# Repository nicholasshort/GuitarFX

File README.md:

# GuitarFX

This is a digital guitar effects pedal designed as a generic DSP platform. I've written simple algorithms such as volume and tone control, however plans are in the works for others: namely hard and soft clipping, digital delay, and much more. The two knobs control various parameters within the current algorithm, including volume or cutoff frequency.

## Hardware

- **MCU**: STM32H723VGT6 (Cortex-M7 @ 550 MHz)
- **Codec**: TI PCM3060 — 24-bit stereo ADC/DAC
- **Analog I/O**: TLV9161 op-amp buffers with 25 kHz Butterworth anti-aliasing and reconstruction filters
- **Audio**: Standard 1/4" guitar input and output, true-bypass footswitch
- **Controls**: 2 × potentiometers, RGB status LED
- **Power**: 9 V DC barrel jack (USB-C can also power the board for bench work)
- **PCB**: 4-layer, KiCad

## Repository layout

- `GuitarFX-PCB/` — KiCad project (schematics, board, libraries)
- `GuitarFX-PCB/Manufacturing/` — Gerbers, BOM, and pick-and-place files for JLCPCB
- `images/` — Photos of the board and enclosure

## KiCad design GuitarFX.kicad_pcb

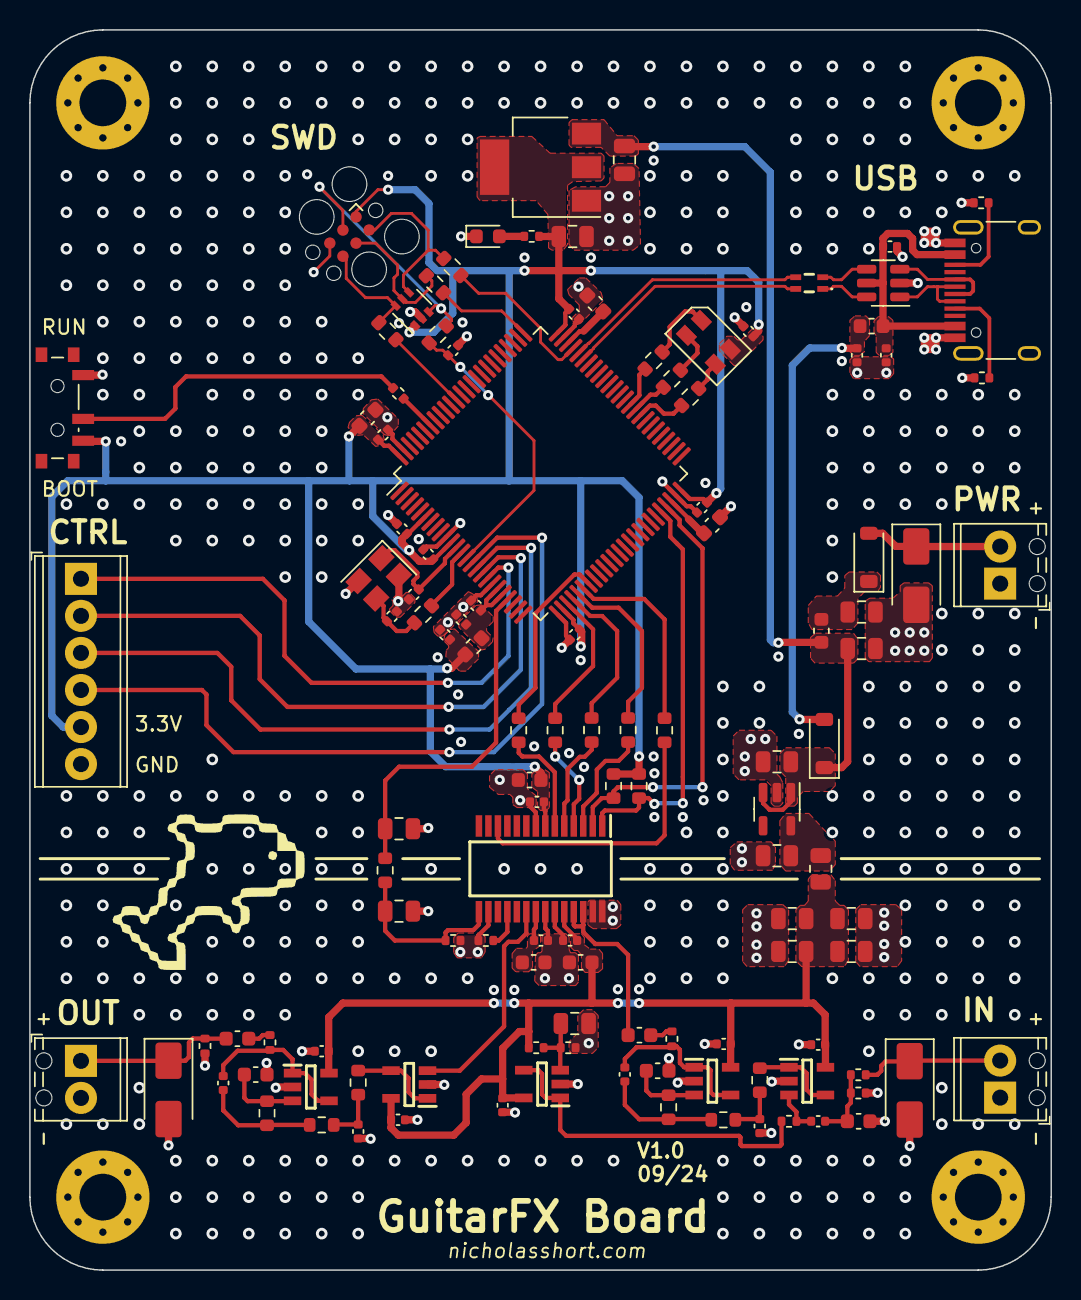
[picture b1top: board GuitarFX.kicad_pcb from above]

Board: 4 copper layers, 70.0 x 85.0 mm, 124 parts (0 on the bottom side), 80 nets.

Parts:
C201, C202, C203, C204: 47uF; C_0805_2012Metric
C205, C206, C207, C208, C411, C412: 2.2uF; C_0805_2012Metric
C209, C210: 10uF; C_0805_2012Metric
C301, C318, C319: 2.2u; C_0603_1608Metric
C302, C303, C304, C305, C306, C307, C308, C309, C310, C311, C312, C313, C316, C317, C402, C403, C404, C420, C421, C429, C431, C433: 100n; C_0402_1005Metric
C314, C315: 10p; C_0402_1005Metric
C401, C409, C419, C423: 1n; C_0402_1005Metric
C405: 22u; C_0805_2012Metric
C406: 10n; C_0402_1005Metric
C407, C422: 4.7u; C_0603_1608Metric
C408, C410, C424: 150p; C_0603_1608Metric
C428, C430, C432: 10u; C_0603_1608Metric
D201, D202: MBR0530; D_SOD-123
D203, D401, D403: SMAJ15A; D_SMA
D204: LED; LED_0603_1608Metric
D302: PESD3V3L5UY; SOT-363_SC-70-6
D303: LED_RGBA; LED_SMD_RGB_AAA3528LSEEZGKQBKS
FB201, FB301, FB302: 120R; L_0603_1608Metric
FL301: ACM2012-900-2P-TL002; ACM20129002PTL002
H101, H102, H103, H104: MountingHole_Pad; MountingHole_3.2mm_M3_Pad_Via
IC401: PCM3060PWR; SOP65P640X120-28N
J202, J401, J402: Screw_Terminal_01x02; TerminalBlock_Phoenix_MPT-0,5-2-2.54_1x02_P2.54mm_Horizontal
J301: USB_C_Receptacle_USB2.0; USB_C_Receptacle_HRO_TYPE-C-31-M-12
J302: Conn_ARM_SWD_TagConnect_TC2030; Tag-Connect_TC2030-IDC-FP_2x03_P1.27mm_Vertical
J303: Screw_Terminal_01x06; TerminalBlock_Phoenix_MPT-0,5-6-2.54_1x06_P2.54mm_Horizontal
R201: 10R; R_0805_2012Metric
R202, R401, R403, R404: 1k; R_0402_1005Metric
R301, R427, R429: 10k; R_0402_1005Metric
R302, R305, R306, R307, R308, R419, R420, R424, R426, R428: 0R; R_0603_1608Metric
R303, R304: 5.1k; R_0402_1005Metric
R309, R310: 325R (300R); R_0603_1608Metric
R311: 750R; R_0603_1608Metric
R402, R409: 1M; R_0402_1005Metric
R405, R421: 8.2k; R_0603_1608Metric
R406, R422: 27k; R_0603_1608Metric
R407, R423: 15k; R_0603_1608Metric
R408, R425: 100R; R_0402_1005Metric
R410: 100k; R_0402_1005Metric
R411: 5.1k; R_0603_1608Metric
R417, R418: 10k; R_0603_1608Metric
SW301: SW_SPDT; SW_SPDT_PCM12
U201: NCP718xSN500; SOT-23-5
U202: NCP1117-3.3_SOT223; SOT-223-3_TabPin2
U301: USBLC6-2SC6; SOT-23-6
U303: STM32H723VGTx; LQFP-100_14x14mm_P0.5mm
U401, U402, U403, U406, U407: TLV9161IDBVR; SOT95P280X145-5N
Y301: 24MHz; Crystal_SMD_3225-4Pin_3.2x2.5mm

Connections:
+3.3V: C209.1, C301.1, C302.1, C303.1, C304.1, C305.1, C306.1, C307.1, C310.1, C317.1, C428.1, C429.1, D302.1 (K1), D303.4 (A), FB301.2, IC401.7 (VDD), J302.1 (VCC), J303.5, R202.1, R417.1, R418.1, SW301.3 (C), U202.2 (VO), U303.6 (VBAT), U303.11 (VDD), U303.27 (VDD), U303.50 (VDD), U303.75 (VDD), U303.100 (VDD)
+5V: C208.1, R201.1, U201.5 (OUT)
+5VA: C201.1, C202.1, C203.1, C204.1, C402.1, C403.1, C404.1, C420.1, C421.1, C430.1, C431.1, IC401.24 (VCC), R201.2, R401.1, U401.5 (V+), U402.5 (V+), U403.5 (V+), U406.5 (V+), U407.5 (V+)
/Codec/AUDIO_VIN: D401.1 (A1), J401.2, R404.1
/Codec/AUDIO_VOUT: C422.1, D403.1 (A1), J402.1, R427.2
/Codec/CODEC_BCK1: IC401.5 (BCK1), R424.2
/Codec/CODEC_DIN: IC401.12 (DIN), R428.2
/Codec/CODEC_DOUT: IC401.3 (DOUT), R419.2
/Codec/CODEC_LRCK1: IC401.4 (LRCK1), R420.2
/Codec/CODEC_SCK1: IC401.6 (SCKI1), R426.2
/Codec/CODEC_VCOM: C432.1, C433.1, IC401.21 (VCOM)
/Codec/CODEC_VIN: C407.1, IC401.25 (VINL), IC401.26 (VINR)
/Codec/CODEC_VOUT: IC401.20 (VOUTL+), U406.3 (+)
/Codec/IN_AA_BUFF_IN: C410.1, R407.2, U403.3 (+)
/Codec/IN_AA_BUFF_OUT: C401.1, R408.1, U403.1, U403.4 (-)
/Codec/IN_BUF_IN: C406.2, R402.1, U402.3 (+)
/Codec/IN_BUF_OUT: R405.1, U402.1, U402.4 (-)
/Codec/IN_RF: C406.1, C408.1, R404.2, R409.2
/Codec/NRST_FILT: C412.1, IC401.15 (~RST), R411.2, R429.1
/Codec/OUT_AA_BUFF_IN: C424.1, R423.2, U407.3 (+)
/Codec/OUT_AA_BUFF_OUT: C419.1, R425.1, U407.1, U407.4 (-)
/Codec/OUT_BUF_OUT: R421.1, U406.1, U406.4 (-)
/Codec/VREF: C405.1, R401.2, R403.1, U401.3 (+)
/MCU/ADC3_INP0: J303.2, U303.17 (PC2_C)
/MCU/ADC3_INP1: J303.1, U303.18 (PC3_C)
/MCU/ADC3_INP10: J303.4, U303.15 (PC0)
/MCU/ADC3_INP11: J303.3, U303.16 (PC1)
/MCU/BOOT0: R301.2, U303.94 (BOOT0)
/MCU/HSE_IN: C314.1, U303.12 (PH0), Y301.1
/MCU/HSE_OUT: R302.2, U303.13 (PH1)
/MCU/LED_B: D303.3 (BK), R309.2
/MCU/LED_G: D303.2 (GK), R310.2
/MCU/LED_R: D303.1 (RK), R311.2
/MCU/MCU_NRST: C316.1, R308.1, U303.14 (NRST)
/MCU/MCU_SWCLK: R306.1, U303.76 (PA14(JTCK)
/MCU/MCU_SWDIO: R305.1, U303.72 (PA13(JTMS)
/MCU/MCU_SWO: R307.1, U303.89 (PB3(JTDO)
/MCU/MCU_VCAP1: C318.1, U303.48 (VCAP)
/MCU/MCU_VCAP2: C319.1, U303.73 (VCAP)
/MCU/NRST: D302.3 (K2), J302.3 (~RESET), R308.2
/MCU/SWCLK: D302.5 (K4), J302.4 (SWCLK), R306.2
/MCU/SWDIO: D302.4 (K3), J302.2 (SWDIO), R305.2
/MCU/SWO: D302.6 (K5), J302.6 (SWO), R307.2
/MCU/TIM4_CH1: R309.1, U303.59 (PD12)
/MCU/TIM4_CH2: R310.1, U303.60 (PD13)
/MCU/TIM4_CH3: R311.1, U303.61 (PD14)
/MCU/USB_CMC_D+: FL301.2, U301.4 (I/O2)
/MCU/USB_CMC_D-: FL301.1, U301.6 (I/O1)
/MCU/USB_CON_CC1: J301.A5 (CC1), R303.1
/MCU/USB_CON_CC2: J301.B5 (CC2), R304.1
/MCU/USB_CON_D+: J301.A6 (D+), J301.B6 (D+), U301.3 (I/O2)
/MCU/USB_CON_D-: J301.A7 (D-), J301.B7 (D-), U301.1 (I/O1)
/MCU/USB_FS_D+: FL301.3, U303.71 (PA12)
/MCU/USB_FS_D-: FL301.4, U303.70 (PA11)
/Power/R_LED: D204.2 (A), R202.2
/Power/VCC_FILT: C206.1, C207.1, C210.1, D201.1 (K), FB201.2, U201.1 (IN), U201.3 (EN), U202.3 (VI)
/Power/VCC_RP: C205.1, D202.1 (K), FB201.1
CODEC_NRST: C411.1, R411.1, U303.22 (PA0)
GND: C201.2, C202.2, C203.2, C204.2, C205.2, C206.2, C207.2, C208.2, C209.2, C210.2, C301.2, C302.2, C303.2, C304.2, C305.2, C306.2, C307.2, C308.2, C309.2, C310.2, C311.2, C312.2, C313.2, C314.2, C315.2, C316.2, C317.2, C318.2, C319.2, C402.2, C403.2, C404.2, C405.2, C408.2, C409.2, C410.2, C411.2, C412.2, C420.2, C421.2, C423.2, C424.2, C428.2, C429.2, C430.2, C431.2, C432.2, C433.2, D203.2 (A2), D204.1 (K), D302.2 (A), D401.2 (A2), D403.2 (A2), H101.1, H102.1, H103.1, H104.1, IC401.8 (DGND), IC401.16 (SGND), IC401.22 (AGND2), IC401.23 (AGND1), IC401.27 (~MS/ADR/IFMD), IC401.28 (MODE), J202.1, J301.A1 (GND), J301.A12 (GND), J301.B1 (GND), J301.B12 (GND), J302.5 (GND), J303.6, J401.1, J402.2, R303.2, R304.2, R403.2, R409.1, R410.2, R427.1, R429.2, SW301.1 (A), U201.2 (GND), U202.1 (GND), U301.2 (GND), U303.10 (VSS), U303.19 (VSSA), U303.26 (VSS), U303.49 (VSS), U303.74 (VSS), U303.99 (VSS), U401.2 (V-), U402.2 (V-), U403.2 (V-), U406.2 (V-), U407.2 (V-), Y301.2, Y301.4
I2C1_SCL: IC401.1 (MC/SCL/FMT), R417.2, U303.46 (PB10)
I2C1_SDA: IC401.2 (MD/SDA/DEMP), R418.2, U303.47 (PB11)
I2S1_CK: R424.1, U303.29 (PA5)
I2S1_MCK: R426.1, U303.32 (PC4)
I2S1_SDI: R419.1, U303.30 (PA6)
I2S1_SDO: R428.1, U303.31 (PA7)
I2S1_WS: R420.1, U303.28 (PA4)
unnamed: C315.1, R302.1, Y301.3
unnamed: C401.2, R406.2, R407.1
unnamed: C407.2, R408.2
unnamed: C409.1, R405.2, R406.1
unnamed: C419.2, R422.2, R423.1
unnamed: C422.2, R425.2
unnamed: C423.1, R421.2, R422.1
unnamed: IC401.18 (VOUTR+), R410.1
unnamed: R301.1, SW301.2 (B)
VBUS: C311.1, C313.1, FB302.1, J301.A4 (VBUS), J301.A9 (VBUS), J301.B4 (VBUS), J301.B9 (VBUS), U301.5 (VBUS)
VCC: D202.2 (A), D203.1 (A1), J202.2
VCOM: R402.2, U401.1, U401.4 (-)
VDDA: C308.1, C309.1, FB301.1, U303.20 (VREF+), U303.21 (VDDA)
VUSB_FILT: C312.1, D201.2 (A), FB302.2

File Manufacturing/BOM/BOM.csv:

Comment,Designator,Footprint,JLCPCB Part #
47uF Unpolarized capacitor,"C201,C202,C203,C204",C_0805_2012Metric,C108659
2.2uF Unpolarized capacitor,"C205,C206,C207,C208,C411,C412",C_0805_2012Metric,C77081
10uF Unpolarized capacitor,"C209,C210",C_0805_2012Metric,C90543
2.2u Unpolarized capacitor,"C301,C318,C319",C_0603_1608Metric,C71001
100n Unpolarized capacitor,"C302,C303,C304,C305,C306,C307,C308,C309,C310,C311,C312,C313,C316,C317,C402,C403,C404,C420,C421,C429,C431,C433",C_0402_1005Metric,C432917
10p Unpolarized capacitor,"C314,C315",C_0402_1005Metric,C258501
1n Unpolarized capacitor,"C401,C409,C419,C423",C_0402_1005Metric,C106205
22u Unpolarized capacitor,C405,C_0805_2012Metric,C129303
10n Unpolarized capacitor,C406,C_0402_1005Metric,C386111
4.7u Unpolarized capacitor,"C407,C422",C_0603_1608Metric,C77045
150p Unpolarized capacitor,"C408,C410,C424",C_0603_1608Metric,C126577
10u Unpolarized capacitor,"C428,C430,C432",C_0603_1608Metric,C380314
"MBR0530 30V 0.5A Schottky Power Rectifier Diode, SOD-123","D201,D202",D_SOD-123,C77336
"SMAJ15A 400W unidirectional Transient Voltage Suppressor, 15.0Vr, SMA(DO-214AC)","D203,D401,D403",D_SMA,C908769
LED Light emitting diode,D204,LED_0603_1608Metric,C5123548
"PESD3V3L5UY Low capacitance unidirectional fivefold ESD protection diode array, 3.3V, Common Anode, SOT-363",D302,SOT-363_SC-70-6,C3021133
"LED_RGBA RGB LED, red/green/blue/anode",D303,LED_SMD_RGB_AAA3528LSEEZGKQBKS,C5547384
120R Ferrite bead,"FB201,FB301,FB302",L_0603_1608Metric,C12391
ACM2012-900-2P-TL002 Common Mode Chokes / Filters -,FL301,ACM20129002PTL002,C3211819
PCM3060PWR 24-bit Asynchronous Stereo Audio Codec with 96/192kHz sampling rate,IC401,SOP65P640X120-28N,C2651841
"Screw_Terminal_01x02 Generic screw terminal, single row, 01x02, script generated (kicad-library-utils/schlib/autogen/connector/)","J202,J401,J402","TerminalBlock_Phoenix_MPT-0,5-2-2.54_1x02_P2.54mm_Horizontal",C3029316
USB_C_Receptacle_USB2.0 USB 2.0-only Type-C Receptacle connector,J301,USB_C_Receptacle_HRO_TYPE-C-31-M-12,C165948
"Screw_Terminal_01x06 Generic screw terminal, single row, 01x06, script generated (kicad-library-utils/schlib/autogen/connector/)",J303,"TerminalBlock_Phoenix_MPT-0,5-6-2.54_1x06_P2.54mm_Horizontal",C3817456
10R Resistor,R201,R_0805_2012Metric,C17415
1k Resistor,"R202,R401,R403,R404",R_0402_1005Metric,C102758
10k Resistor,"R301,R427,R429",R_0402_1005Metric,C176114
33R Resistor,"R302,R305,R306,R307,R308,R419,R420,R424,R426,R428",R_0603_1608Metric,C103557
5.1k Resistor,"R303,R304",R_0402_1005Metric,C325521
325R (300R) Resistor,"R309,R310",R_0603_1608Metric,C137637
750R Resistor,R311,R_0603_1608Metric,C328375
1M Resistor,"R402,R409",R_0402_1005Metric,C409676
8.2k Resistor,"R405,R421",R_0603_1608Metric,C103830
27k Resistor,"R406,R422",R_0603_1608Metric,C116691
15k Resistor,"R407,R423",R_0603_1608Metric,C136588
100R Resistor,"R408,R425",R_0402_1005Metric,C279985
100k Resistor,R410,R_0402_1005Metric,C192169
5.1k Resistor,R411,R_0603_1608Metric,C318133
10k Resistor,"R417,R418",R_0603_1608Metric,C103210
"SW_SPDT Switch, single pole double throw",SW301,SW_SPDT_PCM12,C221841
"NCP718xSN500 300-mA, Wide Input Voltage, Low-IQ LDO, 5.0V, SOT-23",U201,SOT-23-5,C892796
"NCP1117-3.3_SOT223 1A Low drop-out regulator, Fixed Output 3.3V, SOT-223",U202,SOT-223-3_TabPin2,C26537
"USBLC6-2SC6 Very low capacitance ESD protection diode, 2 data-line, SOT-23-6",U301,SOT-23-6,C5261088
"STM32H733VGTx STMicroelectronics Arm Cortex-M7 MCU, 1024KB flash, 564KB RAM, 550 MHz, 1.71-3.6V, 82 GPIO, LQFP100",U302,LQFP-100_14x14mm_P0.5mm,C730160
"TLV9161IDBVR Operational Amplifiers - Op Amps Single 10-MHz, 16-V rail-to-rail input/output, very low noise, high slew rate op amp","U401,U402,U403,U406,U407",SOT95P280X145-5N,C4368955
"24MHz Four pin crystal, GND on pins 2 and 4",Y301,Crystal_SMD_3225-4Pin_3.2x2.5mm,C5308005

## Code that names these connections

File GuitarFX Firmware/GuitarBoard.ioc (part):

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Mcu.Name=STM32H723VGTx
Mcu.Package=LQFP100
Mcu.UserName=STM32H723VGTx
PA0.GPIOParameters=GPIO_Label
PA0.GPIO_Label=CODEC_NRST
PA0.Signal=GPIO_Output
PA13(JTMS/SWDIO).Mode=Trace_Asynchronous_SW
PA13(JTMS/SWDIO).Signal=DEBUG_JTMS-SWDIO
PA14(JTCK/SWCLK).Mode=Trace_Asynchronous_SW
PA14(JTCK/SWCLK).Signal=DEBUG_JTCK-SWCLK
PA4.Mode=Full_Duplex_Master
PA4.Signal=I2S1_WS
PA5.Mode=Full_Duplex_Master
PA5.Signal=I2S1_CK
PA6.Mode=Full_Duplex_Master
PA6.Signal=I2S1_SDI
PA7.Mode=Full_Duplex_Master
PA7.Signal=I2S1_SDO
PB10.Mode=I2C
PB10.Signal=I2C2_SCL
PB11.Mode=I2C
PB11.Signal=I2C2_SDA
PB3(JTDO/TRACESWO).Mode=Trace_Asynchronous_SW
PB3(JTDO/TRACESWO).Signal=DEBUG_JTDO-SWO
PC4.Mode=Master_Clock_Activated
PC4.Signal=I2S1_MCK
PD12.Signal=S_TIM4_CH1
PD13.Signal=S_TIM4_CH2
PD14.Signal=S_TIM4_CH3
PH0-OSC_IN.Mode=HSE-External-Oscillator
PH0-OSC_IN.Signal=RCC_OSC_IN
PH1-OSC_OUT.Mode=HSE-External-Oscillator
PH1-OSC_OUT.Signal=RCC_OSC_OUT
RCC.HSE_VALUE=24000000
RCC.SYSCLKFreq_VALUE=550000000
RCC.SYSCLKSource=RCC_SYSCLKSOURCE_PLLCLK
board=custom

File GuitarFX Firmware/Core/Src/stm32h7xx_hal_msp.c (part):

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
    __HAL_RCC_GPIOB_CLK_ENABLE();
    /**I2C2 GPIO Configuration
    PB10     ------> I2C2_SCL
    PB11     ------> I2C2_SDA
    */
    GPIO_InitStruct.Pin = GPIO_PIN_10|GPIO_PIN_11;
    GPIO_InitStruct.Mode = GPIO_MODE_AF_OD;
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    __HAL_RCC_I2C2_CLK_DISABLE();

    /**I2C2 GPIO Configuration
    PB10     ------> I2C2_SCL
    PB11     ------> I2C2_SDA
    */
    HAL_GPIO_DeInit(GPIOB, GPIO_PIN_10);

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    __HAL_RCC_GPIOA_CLK_ENABLE();
    __HAL_RCC_GPIOC_CLK_ENABLE();
    /**I2S1 GPIO Configuration
    PA4     ------> I2S1_WS
    PA5     ------> I2S1_CK
    PA6     ------> I2S1_SDI
    PA7     ------> I2S1_SDO
    PC4     ------> I2S1_MCK
    */
    GPIO_InitStruct.Pin = GPIO_PIN_4|GPIO_PIN_5|GPIO_PIN_6|GPIO_PIN_7;
    GPIO_InitStruct.Mode = GPIO_MODE_AF_PP;
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    __HAL_RCC_SPI1_CLK_DISABLE();

    /**I2S1 GPIO Configuration
    PA4     ------> I2S1_WS
    PA5     ------> I2S1_CK
    PA6     ------> I2S1_SDI
    PA7     ------> I2S1_SDO
    PC4     ------> I2S1_MCK
    */
    HAL_GPIO_DeInit(GPIOA, GPIO_PIN_4|GPIO_PIN_5|GPIO_PIN_6|GPIO_PIN_7);

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
    __HAL_RCC_GPIOD_CLK_ENABLE();
    /**TIM4 GPIO Configuration
    PD12     ------> TIM4_CH1
    PD13     ------> TIM4_CH2
    PD14     ------> TIM4_CH3
    */
    GPIO_InitStruct.Pin = GPIO_PIN_12|GPIO_PIN_13|GPIO_PIN_14;
    GPIO_InitStruct.Mode = GPIO_MODE_AF_PP;
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
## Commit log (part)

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2024-07-19 Empty project
2024-07-25 Started power section
2024-07-26 Finished power schematic
2024-07-26 Annotating schematic and fixing mistake
2024-07-26 Added power led to power schematic
2024-07-31 Added decuopling capacitors and filtering to MCU
2024-08-06 Finished crystal oscillator circuit
2024-08-15 Finished tag connect SWD connections on schematic
2024-08-16 Added USB-C connector to schematic and changed inductors in filters to ferrites
2024-08-24 Added decoupling caps to codec
2024-08-25 Finished i2s and i2c connections on codec and mcu
2024-09-15 Added new codec: PCM3060
2024-09-16 Added connections to CODEC
2024-09-17 Refactored CODEC and added opamp for analog front end
2024-09-17 Added RGB LEDs and ADC connections for potentiometer readings along with connector
2024-09-17 Completed Analog Frontend schematic
2024-09-17 Added bias generator
2024-09-18 Fixed capactor value on frontend
2024-09-18 Completed the 'Rearend' lmao
2024-09-18 Got rid of most ERC violations
2024-09-18 Updated footprints for capacitors
2024-09-18 Created RGB LED footprint
2024-09-22 Assigned all footprints
2024-09-22 Fixed footprints for some components
2024-09-22 Changed butterworth filter components to 0603 for easier resoldering
2024-09-22 Updated USBC connector part and confirmed it is on JLC
2024-09-22 Corrected glitched old save for footprint assignment
2024-09-23 Completed board setup
2024-09-23 Updating 3D models for each component
2024-09-23 Finished rough layout for MCU
2024-09-23 Changed to mono input, and finished rough Analog Frontend layout
2024-09-25 Finished rough layout
2024-09-25 Added mounting holes
2024-09-25 Made position changes to nicer coordinates, and added edge cuts
2024-09-25 Pre routing commit
2024-09-25 Routed mcu decoupling caps and crystal
2024-09-25 USB routing complete
2024-09-26 Finished routing for i2s
2024-09-26 Updated I2C pins for easier routing
2024-09-26 SWD routing done
2024-09-26 RGB led routing complete
2024-09-26 Routing complete for ADC section
2024-09-27 DAC portion routed
2024-09-27 Finished routing LDO sections
2024-09-27 5VA Power routing complete
2024-09-27 Finished 3V power routing
2024-09-27 Added pi filter for Codec NRST signal
2024-09-28 Completed ADC terminal block connections. Finished routing
2024-09-28 Fixed errors in DRC
2024-09-28 Added stitching vias
2024-09-28 Added silkscreen and tidied up component positioning
2024-09-29 Added JLCPCB part numbers for main hardware components to order them
2024-10-02 Refactoring
2024-10-13 Updated 33R resistors to 0R and changed MCU to H723 from H733
2024-10-13 Updated butterworth fc to 25khz, and changed jlc part numbers for resitors and caps
2024-10-14 Removed CMC and generated new production files
2026-06-29 Cleaning up repo
2026-06-29 Adding README
2026-06-29 Cleaning up README

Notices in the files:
GuitarFX Firmware/Core/Src/stm32h7xx_hal_msp.c:
Copyright (c) 2024 STMicroelectronics.
All rights reserved.
This software is licensed under terms that can be found in the LICENSE file
